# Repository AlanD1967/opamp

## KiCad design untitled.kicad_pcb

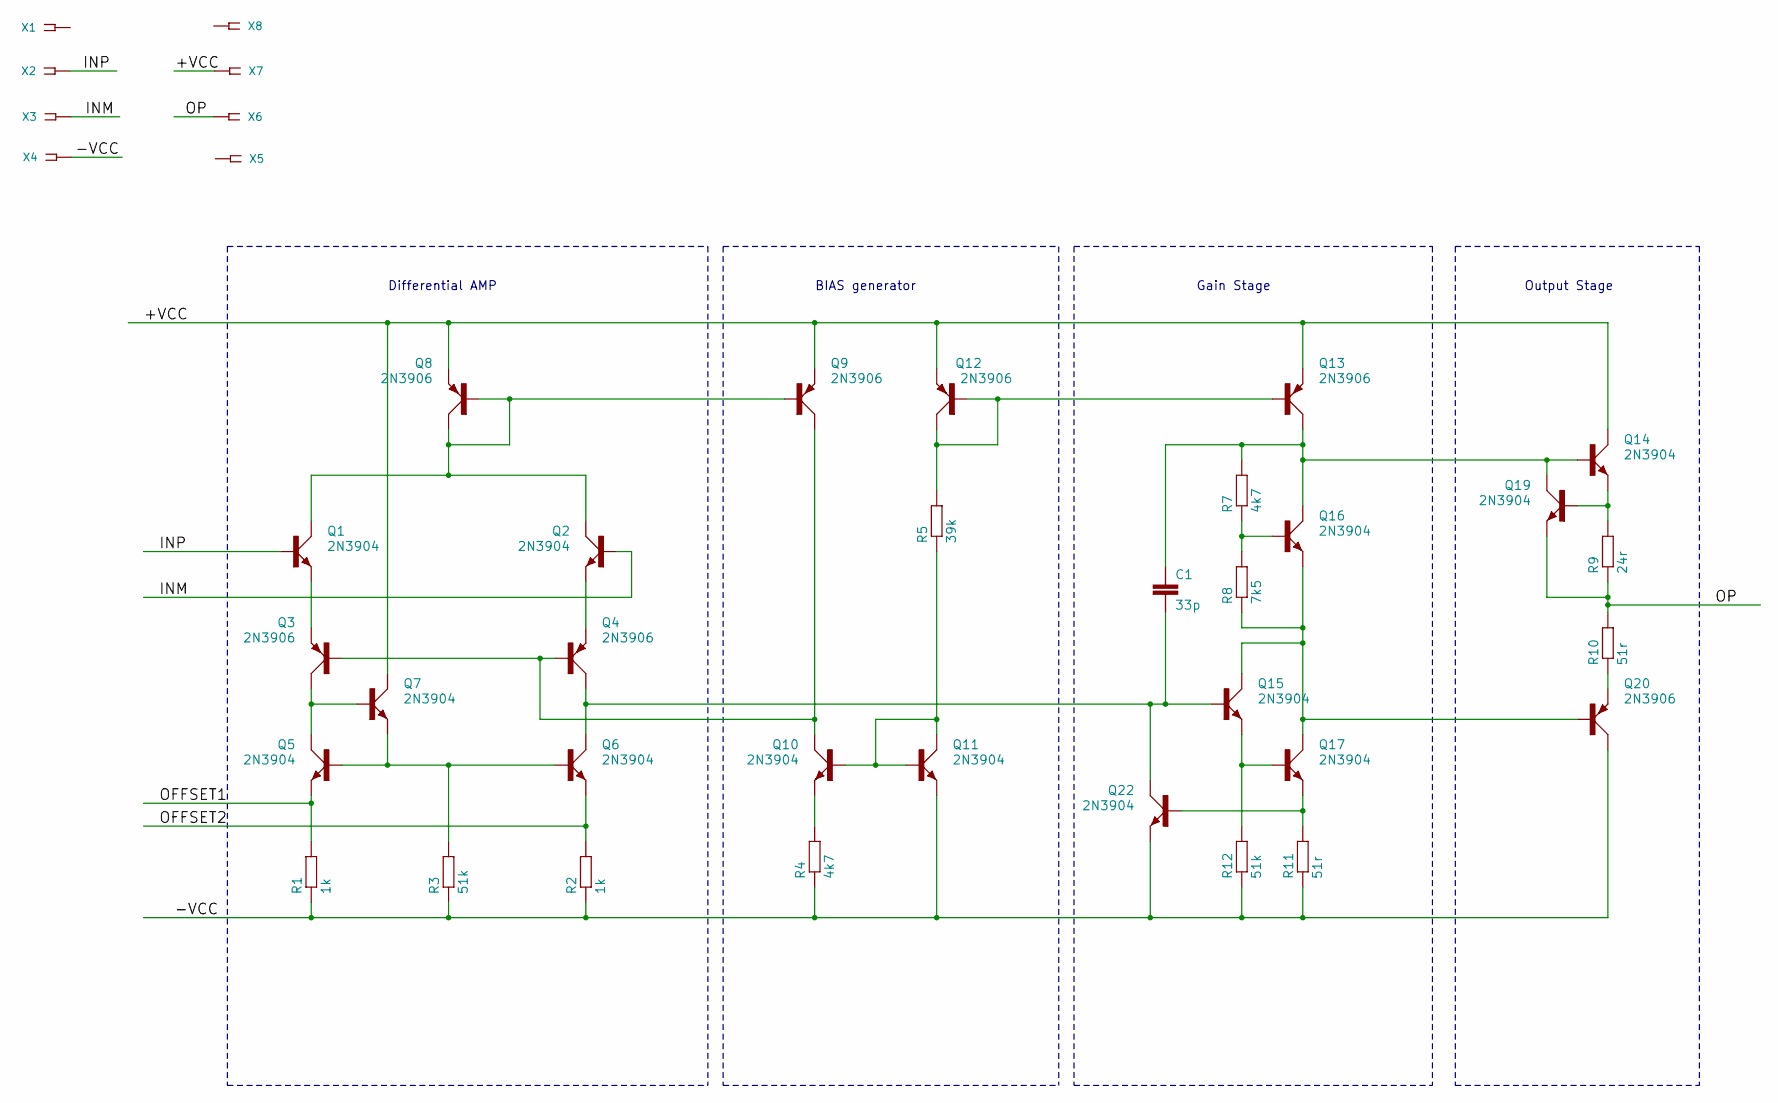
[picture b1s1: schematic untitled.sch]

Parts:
C1: 33p; C025-024X044
Q1, Q2, Q5, Q6, Q7, Q10, Q11, Q14, Q15, Q16, Q17, Q19, Q22: 2N3904; TO92D
Q3, Q4, Q8, Q9, Q12, Q13, Q20: 2N3906; TO92D
R1, R2: 1k; 0204_5
R3, R12: 51k; 0204_5
R4, R7: 4k7; 0204_5
R5: 39k; 0204_5
R8: 7k5; 0204_5
R9: 24r; 0204_5
R10, R11: 51r; 0204_5
X1, X2, X3, X4, X5, X6, X7, X8: SSW-101-02-S-S

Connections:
/+VCC: Q7.C, Q8.E, Q9.E, Q12.E, Q13.E, Q14.C, X7.1
/-VCC: Q11.E, Q20.C, Q22.E, R1.1, R2.1, R3.1, R4.1, R11.1, R12.1, X4.1
/INM: Q2.B, X3.1
/INP: Q1.B, X2.1
/OFFSET1: Q5.E, R1.2
/OFFSET2: Q6.E, R2.2
/OP: Q19.E, R9.1, R10.2, X6.1
unnamed: C1.1, Q13.C, Q14.B, Q16.C, Q19.C, R7.2
unnamed: C1.2, Q4.C, Q6.C, Q15.B, Q22.C
unnamed: Q1.C, Q2.C, Q8.B, Q8.C, Q9.B
unnamed: Q1.E, Q3.E
unnamed: Q2.E, Q4.E
unnamed: Q3.C, Q5.C, Q7.B
unnamed: Q5.B, Q6.B, Q7.E, R3.2
unnamed: Q10.B, Q11.B, Q11.C, R5.1
unnamed: Q3.B, Q4.B, Q9.C, Q10.C
unnamed: Q10.E, R4.2
unnamed: Q12.B, Q12.C, Q13.B, R5.2
unnamed: Q14.E, Q19.B, R9.2
unnamed: Q15.C, Q16.E, Q17.C, Q20.B, R8.1
unnamed: Q15.E, Q17.B, R12.2
unnamed: Q16.B, R7.1, R8.2
unnamed: Q17.E, Q22.B, R11.2
unnamed: Q20.E, R10.1

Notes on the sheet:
Differential AMP
BIAS generator
Gain Stage
Output Stage

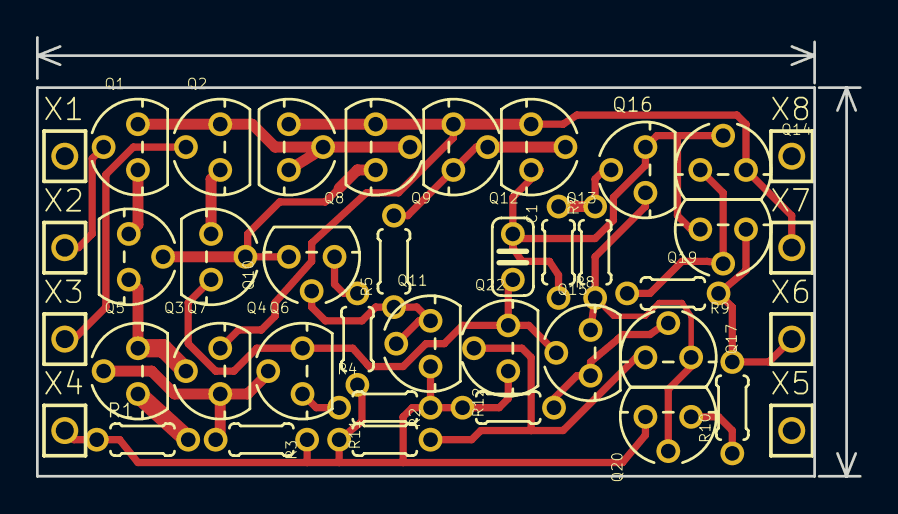
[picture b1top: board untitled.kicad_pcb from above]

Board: 2 copper layers, 45.7 x 24.4 mm, 40 parts (0 on the bottom side), 24 nets.

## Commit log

2020-01-24 opamp
2020-02-04 4feb2020
